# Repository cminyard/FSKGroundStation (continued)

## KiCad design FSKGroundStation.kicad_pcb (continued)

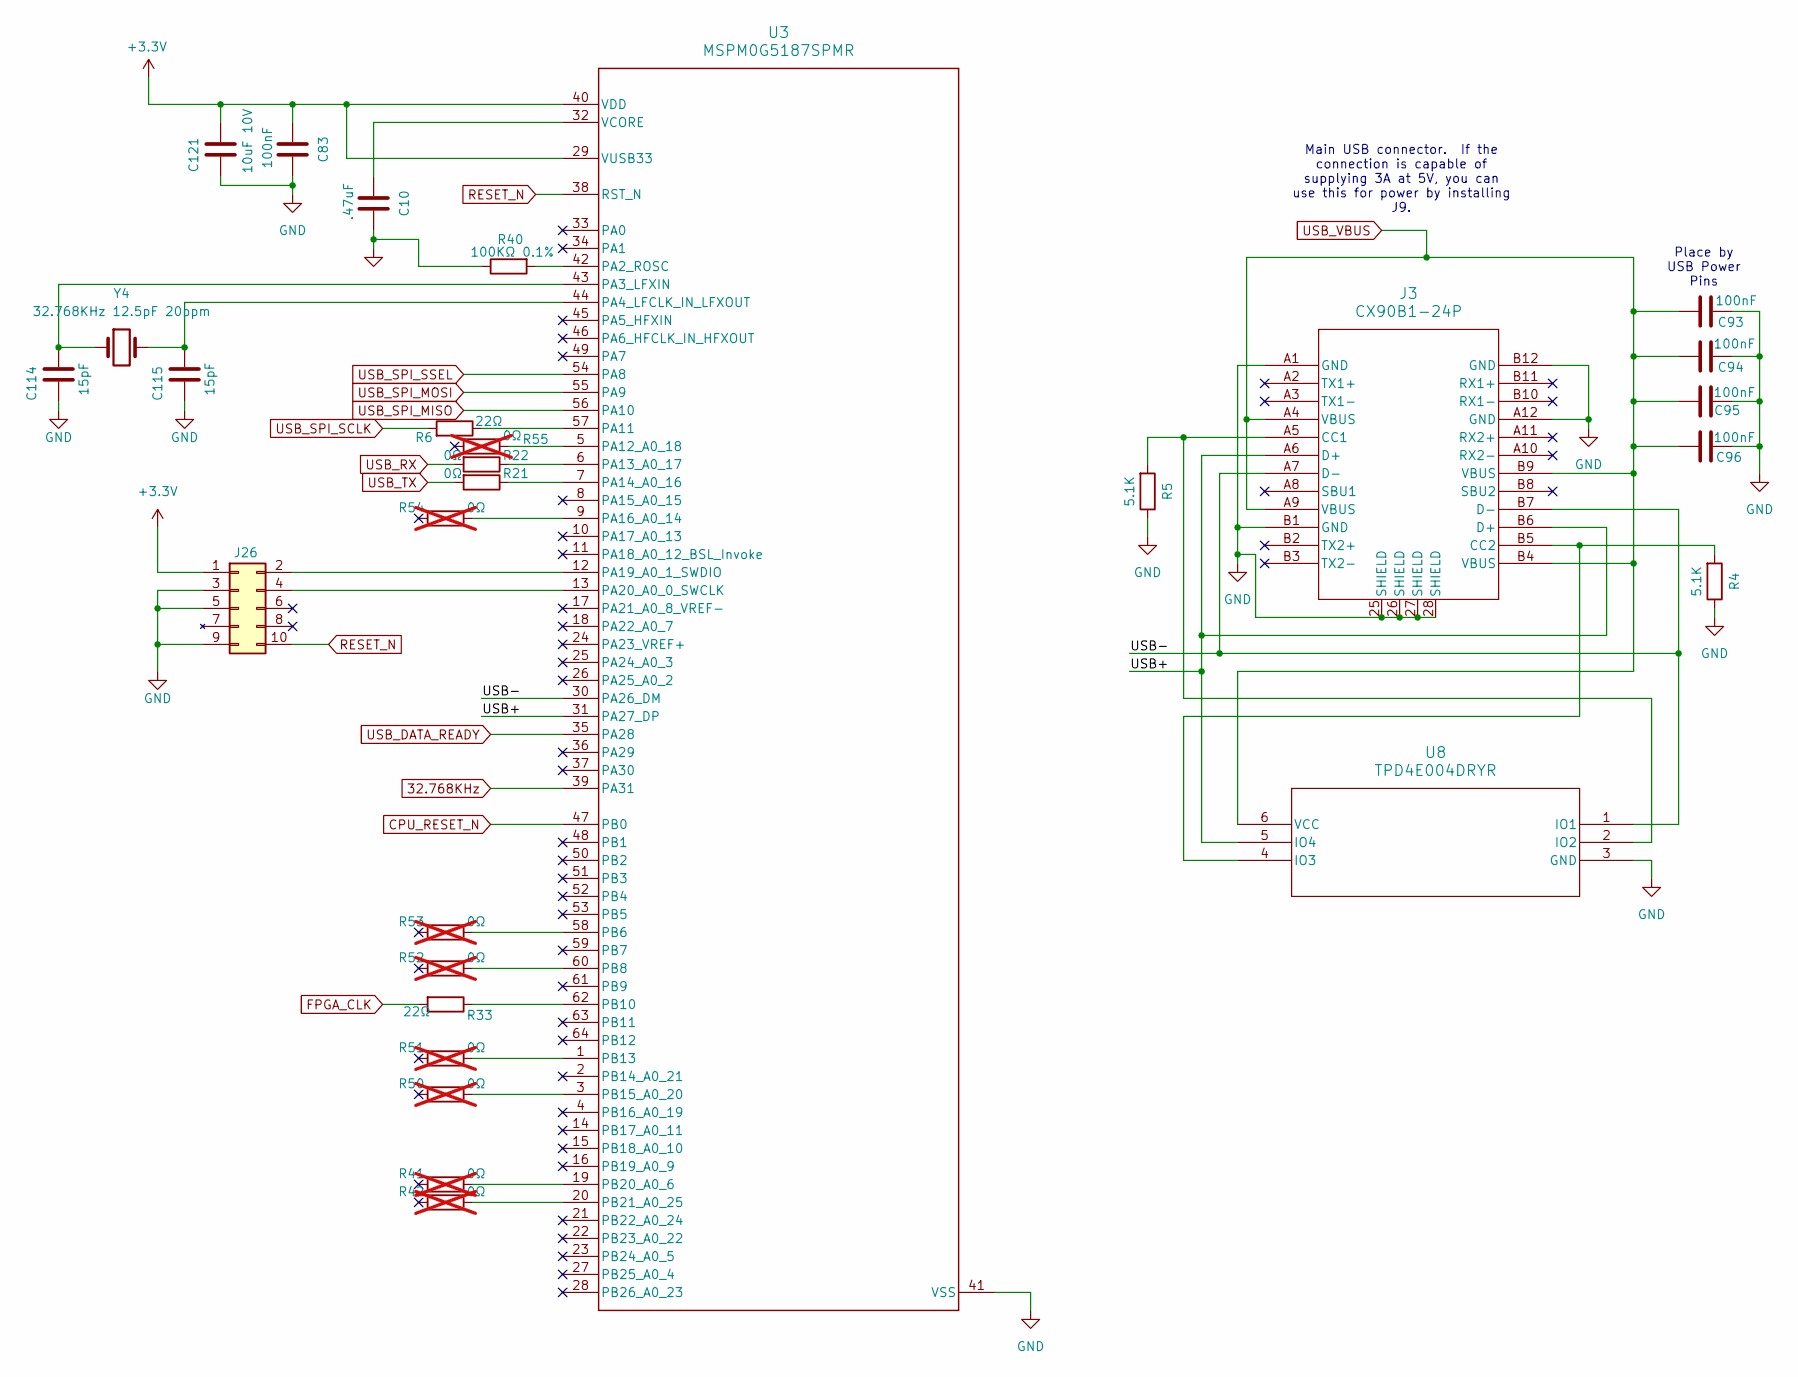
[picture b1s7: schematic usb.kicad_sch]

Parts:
C10: .47uF; C_0603_1608Metric_Pad1.08x0.95mm_HandSolder
C83, C93, C94, C95, C96: 100nF; C_0402_1005Metric
C114, C115: 15pF; C_0402_1005Metric_Pad0.74x0.62mm_HandSolder
C121: 10uF 10V; C_1206_3216Metric_Pad1.33x1.80mm_HandSolder
J3: CX90B1-24P; CX90B1-24P_HIR
J26: FTSH-105-01-L-DV-K
R4, R5: 5.1K; R_0402_1005Metric
R6: 22Ω; R_0402_1005Metric
R21, R22: 0Ω; R_0402_1005Metric
R33: 22Ω; R_0402_1005Metric_Pad0.72x0.64mm_HandSolder
R40: 100KΩ 0.1%; R_0402_1005Metric
R41, R42, R50, R51, R52, R53, R54, R55: 0Ω; R_0402_1005Metric; not fitted
U3: MSPM0G5187SPMR; PM0064A-IPC_A
U8: TPD4E004DRYR; DRY6
Y4: 32.768KHz 12.5pF 20ppm; Crystal_SMD_2012-2Pin_2.0x1.2mm

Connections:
32.768KHz: U3.39 (PA31); also elsewhere on the board
+3.3V: C83.2, C121.2, J26.1 (VTREF), U3.29 (VUSB33), U3.40 (VDD); also elsewhere on the board
/USB/USB+: J3.A6 (D+), J3.B6 (D+), U3.31 (PA27_DP), U8.5 (IO4)
/USB/USB-: J3.A7 (D-), J3.B7 (D-), U3.30 (PA26_DM), U8.1 (IO1)
CPU_RESET_N: U3.47 (PB0); also elsewhere on the board
FPGA_CLK: R33.2; also elsewhere on the board
GND: C10.1, C83.1, C93.2, C94.2, C95.2, C96.2, C114.1, C115.1, C121.1, J3.25 (SHIELD), J3.26 (SHIELD), J3.27 (SHIELD), J3.28 (SHIELD), J3.A1 (GND), J3.A12 (GND), J3.B1 (GND), J3.B12 (GND), J26.3 (GND), J26.5 (GND), J26.9 (GND), R4.1, R5.1, R40.1, U3.41 (VSS), U8.3 (GND); also elsewhere on the board
unnamed: J3.A5 (CC1), R5.2, U8.2 (IO2)
unnamed: J3.B5 (CC2), R4.2, U8.4 (IO3)
unnamed: J26.4 (TCK), U3.13 (PA20_A0_0_SWCLK)
unnamed: J26.2 (TMS), U3.12 (PA19_A0_1_SWDIO)
unnamed: R40.2, U3.42 (PA2_ROSC)
unnamed: C114.2, U3.43 (PA3_LFXIN), Y4.1
unnamed: C115.2, U3.44 (PA4_LFCLK_IN_LFXOUT), Y4.2
unnamed: R6.1, U3.57 (PA11)
unnamed: R55.1, U3.5 (PA12_A0_18)
unnamed: R22.1, U3.6 (PA13_A0_17)
unnamed: R21.1, U3.7 (PA14_A0_16)
unnamed: R54.1, U3.9 (PA16_A0_14)
unnamed: R53.1, U3.58 (PB6)
unnamed: R52.1, U3.60 (PB8)
unnamed: R33.1, U3.62 (PB10)
unnamed: R51.1, U3.1 (PB13)
unnamed: R50.1, U3.3 (PB15_A0_20)
unnamed: R41.1, U3.19 (PB20_A0_6)
unnamed: R42.1, U3.20 (PB21_A0_25)
unnamed: C10.2, U3.32 (VCORE)
RESET_N: J26.10 (NRST), U3.38 (RST_N); also elsewhere on the board
USB_DATA_READY: U3.35 (PA28); also elsewhere on the board
USB_RX: R22.2; also elsewhere on the board
USB_SPI_MISO: U3.56 (PA10); also elsewhere on the board
USB_SPI_MOSI: U3.55 (PA9); also elsewhere on the board
USB_SPI_SCLK: R6.2; also elsewhere on the board
USB_SPI_SSEL: U3.54 (PA8); also elsewhere on the board
USB_TX: R21.2; also elsewhere on the board
USB_VBUS: C93.1, C94.1, C95.1, C96.1, J3.A4 (VBUS), J3.A9 (VBUS), J3.B4 (VBUS), J3.B9 (VBUS), U8.6 (VCC); also elsewhere on the board

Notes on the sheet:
Place by USB Power Pins
Main USB connector. If the connection is capable of supplying 3A at 5V, you can use this for power by installing J9.

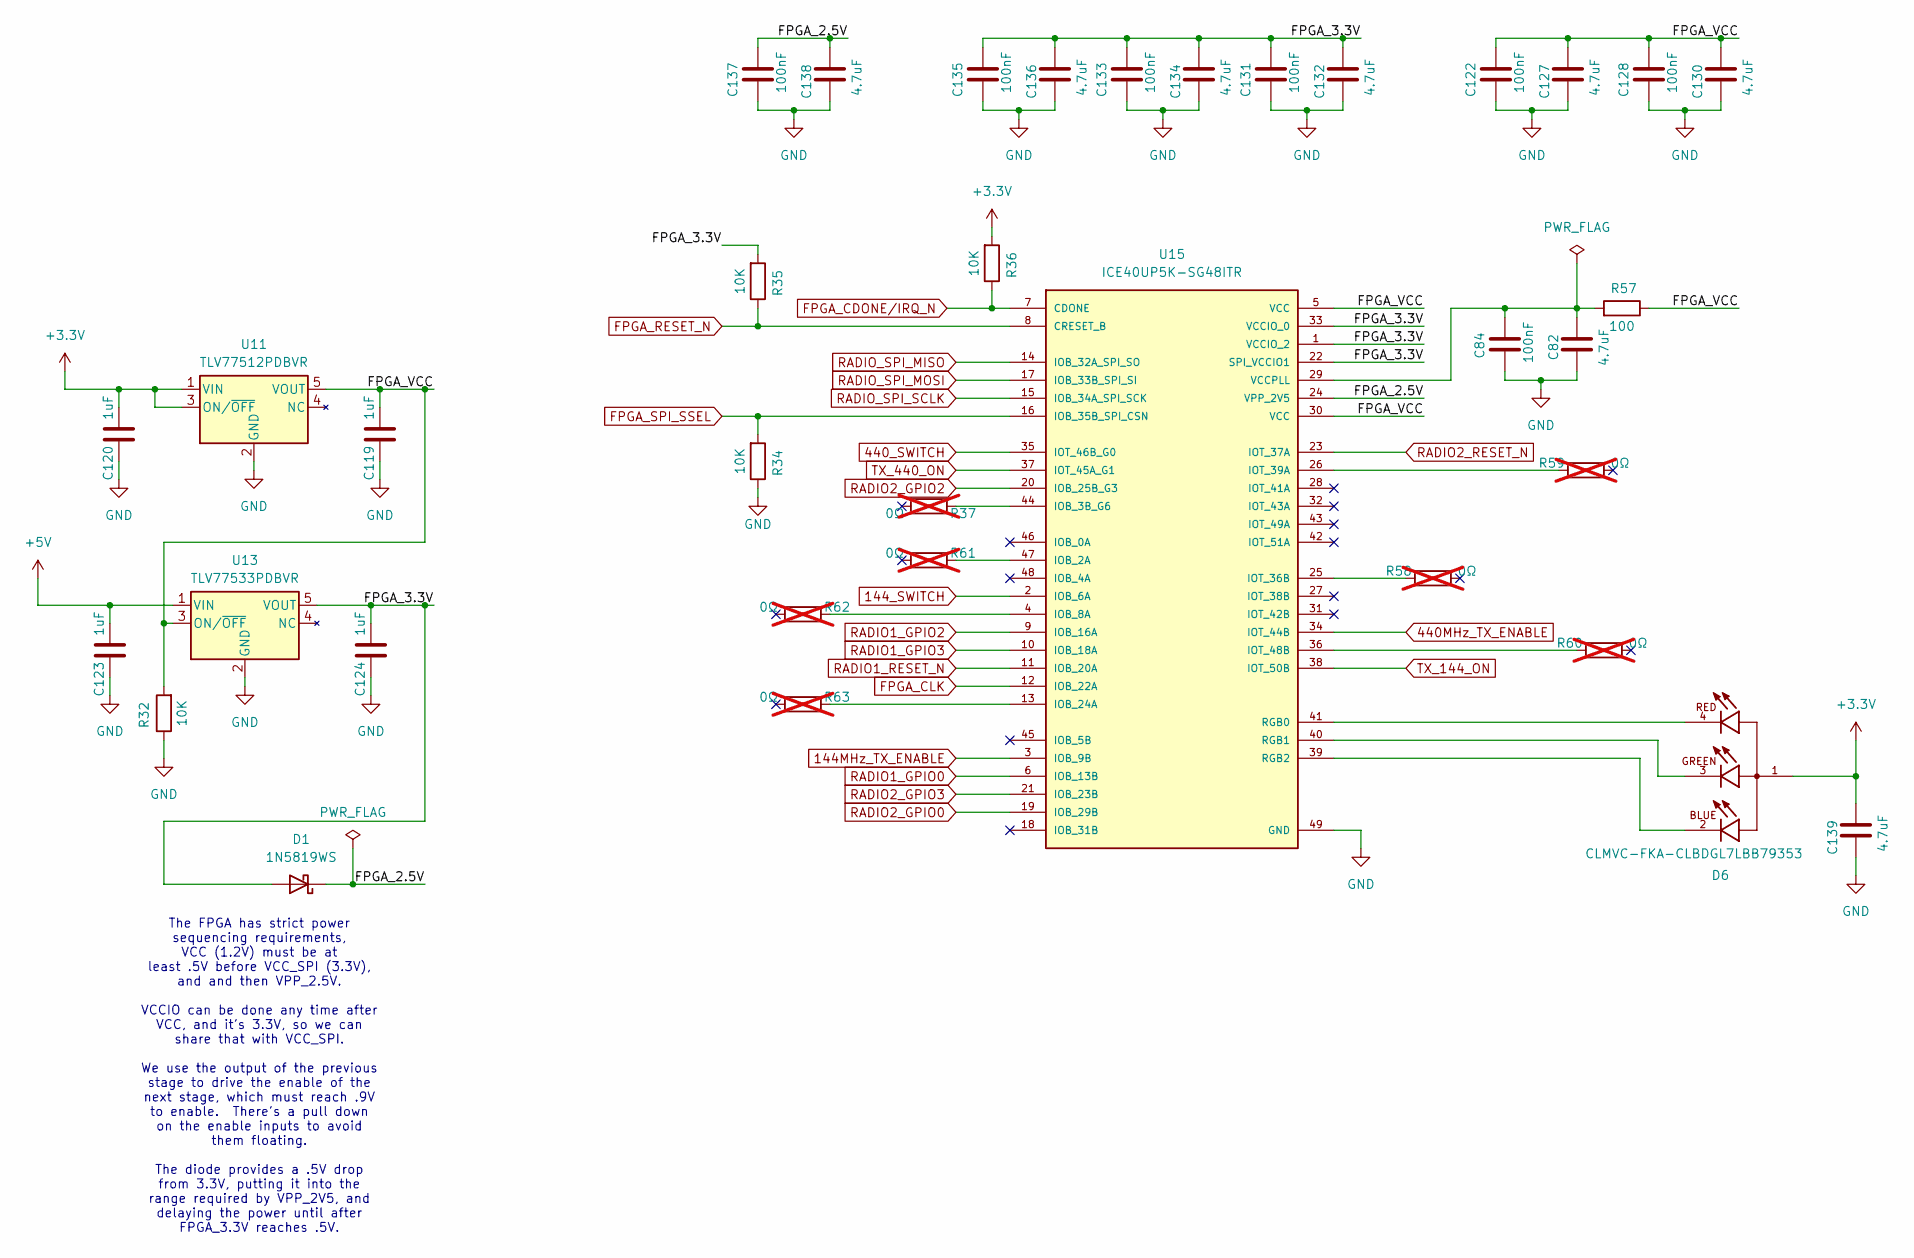
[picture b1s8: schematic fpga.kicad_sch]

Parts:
C82, C127, C130, C132, C134, C136, C138, C139: 4.7uF; C_0603_1608Metric_Pad1.08x0.95mm_HandSolder
C84, C122, C128, C131, C133, C135, C137: 100nF; C_0402_1005Metric_Pad0.74x0.62mm_HandSolder
C119, C120, C123, C124: 1uF; C_0603_1608Metric_Pad1.08x0.95mm_HandSolder
D1: 1N5819WS; D_SOD-323
D6: CLMVC-FKA-CLBDGL7LBB79353; LED_CLMVC-FKA-CLBDGL7LBB79353; PARTREV 14
R32, R34, R35, R36: 10K; R_0402_1005Metric
R37, R58, R59, R60, R61, R62, R63: 0Ω; R_0402_1005Metric_Pad0.72x0.64mm_HandSolder; not fitted
R57: 100; R_0402_1005Metric
U11: TLV77512PDBVR; SOT-23-5
U13: TLV77533PDBVR; SOT-23-5
U15: ICE40UP5K-SG48ITR; QFN50P700X700X100-49N; DigiKey_Part_Number 220-2155-1-ND

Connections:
144MHz_TX_ENABLE: U15.3 (IOB_9B); also elsewhere on the board
144_SWITCH: U15.2 (IOB_6A); also elsewhere on the board
440MHz_TX_ENABLE: U15.34 (IOT_44B); also elsewhere on the board
440_SWITCH: U15.35 (IOT_46B_G0); also elsewhere on the board
+3.3V: C120.2, C139.2, D6.1, R36.2, U11.1 (VIN), U11.3 (ON/~OFF); also elsewhere on the board
+5V: C123.2, U13.1 (VIN); also elsewhere on the board
/FPGA/FPGA_2.5V: C137.2, C138.2, D1.1 (K), U15.24 (VPP_2V5)
/FPGA/FPGA_3.3V: C124.2, C131.2, C132.2, C133.2, C134.2, C135.2, C136.2, D1.2 (A), R35.2, U13.5 (VOUT), U15.1 (VCCIO_2), U15.22 (SPI_VCCIO1), U15.33 (VCCIO_0)
/FPGA/FPGA_VCC: C119.2, C122.2, C127.2, C128.2, C130.2, R32.2, R57.1, U11.5 (VOUT), U13.3 (ON/~OFF), U15.5 (VCC), U15.30 (VCC)
FPGA_CDONE/IRQ_N: R36.1, U15.7 (CDONE); also elsewhere on the board
FPGA_CLK: U15.12 (IOB_22A); also elsewhere on the board
FPGA_RESET_N: R35.1, U15.8 (CRESET_B); also elsewhere on the board
FPGA_SPI_SSEL: R34.2, U15.16 (IOB_35B_SPI_CSN); also elsewhere on the board
GND: C82.1, C84.1, C119.1, C120.1, C122.1, C123.1, C124.1, C127.1, C128.1, C130.1, C131.1, C132.1, C133.1, C134.1, C135.1, C136.1, C137.1, C138.1, C139.1, R32.1, R34.1, U11.2 (GND), U13.2 (GND), U15.49 (GND); also elsewhere on the board
unnamed: R61.1, U15.47 (IOB_2A)
unnamed: R37.1, U15.44 (IOB_3B_G6)
unnamed: R62.1, U15.4 (IOB_8A)
unnamed: R63.1, U15.13 (IOB_24A)
unnamed: R58.1, U15.25 (IOT_36B)
unnamed: R59.1, U15.26 (IOT_39A)
unnamed: R60.1, U15.36 (IOT_48B)
unnamed: D6.4, U15.41 (RGB0)
unnamed: D6.3, U15.40 (RGB1)
unnamed: D6.2, U15.39 (RGB2)
unnamed: C82.2, C84.2, R57.2, U15.29 (VCCPLL)
RADIO1_GPIO0: U15.6 (IOB_13B); also elsewhere on the board
RADIO1_GPIO2: U15.9 (IOB_16A); also elsewhere on the board
RADIO1_GPIO3: U15.10 (IOB_18A); also elsewhere on the board
RADIO1_RESET_N: U15.11 (IOB_20A); also elsewhere on the board
RADIO2_GPIO0: U15.19 (IOB_29B); also elsewhere on the board
RADIO2_GPIO2: U15.20 (IOB_25B_G3); also elsewhere on the board
RADIO2_GPIO3: U15.21 (IOB_23B); also elsewhere on the board
RADIO2_RESET_N: U15.23 (IOT_37A); also elsewhere on the board
RADIO_SPI_MISO: U15.14 (IOB_32A_SPI_SO); also elsewhere on the board
RADIO_SPI_MOSI: U15.17 (IOB_33B_SPI_SI); also elsewhere on the board
RADIO_SPI_SCLK: U15.15 (IOB_34A_SPI_SCK); also elsewhere on the board
TX_144_ON: U15.38 (IOT_50B); also elsewhere on the board
TX_440_ON: U15.37 (IOT_45A_G1); also elsewhere on the board

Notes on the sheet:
The FPGA has strict power sequencing requirements, VCC (1.2V) must be at least .5V before VCC_SPI (3.3V), and and then VPP_2.5V. VCCIO can be done any time after VCC, and it's 3.3V, so we can share that with VCC_SPI. We use the output of the previous stage to drive the enable of the next stage, whi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

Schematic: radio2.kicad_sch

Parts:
C14: 10nF; C_0402_1005Metric_Pad0.74x0.62mm_HandSolder
C16, C29: 1nF; C_0402_1005Metric_Pad0.74x0.62mm_HandSolder
C17, C18, C19, C20, C21, C22, C23, C24, C25, C26, C27: 47nF; C_0402_1005Metric_Pad0.74x0.62mm_HandSolder
C28: 220nF; C_0402_1005Metric_Pad0.74x0.62mm_HandSolder
C49: 39pF 1%; C_0402_1005Metric_Pad0.74x0.62mm_HandSolder
C53: 56pF 1%; C_0402_1005Metric_Pad0.74x0.62mm_HandSolder
C85: 100nF; C_0402_1005Metric_Pad0.74x0.62mm_HandSolder
L18: 56nH; L_0603_1608Metric_Pad1.05x0.95mm_HandSolder
R7: 56K 1%; R_0402_1005Metric
R14: 0Ω; R_0402_1005Metric
R16: 18Ω; R_0402_1005Metric
R31: 0Ω; R_0402_1005Metric; not fitted
U14: CC1125RHBR; RHB32_3P45X3P45_TEX
Y1: OW2EL89CENUXK7YLC-40M; Oscillator_SMD_SiT_PQFN-4Pin_2.0x1.6mm

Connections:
440_PA: C49.2; also elsewhere on the board
440_RX_N: U14.20 (LNA_N); also elsewhere on the board
440_RX_P: U14.19 (LNA_P); also elsewhere on the board
440_TRX_SW: U14.18 (TRX_SW); also elsewhere on the board
+3.3V: C19.2, C20.2, C21.2, C22.2, C23.2, C24.2, C25.2, C26.2, C27.2, C53.2, C85.2, R16.2, U14.1 (VDD_GUARD), U14.5 (DVDD), U14.12 (DVDD), U14.13 (AVDD_IF), U14.15 (AVDD_RF), U14.22 (AVDD_SYNTH1), U14.25 (AVDD_PFD_CHP), U14.27 (AVDD_SYNTH2), U14.28 (AVDD_XOSC), Y1.4 (V+); also elsewhere on the board
GND: C14.1, C17.1, C18.1, C19.1, C20.1, C21.1, C22.1, C23.1, C24.1, C25.1, C26.1, C27.1, C28.1, C85.1, R7.1, R31.1, U14.30 (XOSC_Q1), U14.33 (EPAD), Y1.2 (GND); also elsewhere on the board
unnamed: C29.2, R14.1, R31.2
unnamed: C53.1, L18.2, R16.1
unnamed: C28.2, U14.6 (DCPL)
unnamed: C18.2, U14.26 (DCPL_PFD_CHP)
unnamed: C14.2, U14.21 (DCPL_VCO)
unnamed: C17.2, U14.29 (DCPL_XOSC)
unnamed: C29.1, U14.32 (EXT_XOSC)
unnamed: C16.1, U14.23 (LPF0)
unnamed: C16.2, U14.24 (LPF1)
unnamed: C49.1, L18.1, U14.17 (PA)
unnamed: R7.2, U14.14 (RBIAS)
unnamed: R14.2, Y1.3 (OUT)
RADIO2_GPIO0: U14.10 (GPIO0); also elsewhere on the board
RADIO2_GPIO2: U14.4 (GPIO2); also elsewhere on the board
RADIO2_GPIO3: U14.3 (GPIO3); also elsewhere on the board
RADIO2_RESET_N: U14.2 (RESET_N); also elsewhere on the board
RADIO2_SPI_SSEL: U14.11 (CSN); also elsewhere on the board
RADIO_SPI_MISO: U14.9 (SO(GPIO1)); also elsewhere on the board
RADIO_SPI_MOSI: U14.7 (SI); also elsewhere on the board
RADIO_SPI_SCLK: U14.8 (SCLK); also elsewhere on the board

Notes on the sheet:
This is in case we need to reduce the voltage into the oscillator pin.
Decoupling, place one by each power pin.

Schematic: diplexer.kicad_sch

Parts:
C112: 5pF ±.1; C_0402_1005Metric_Pad0.74x0.62mm_HandSolder
C129: 14pF 1%; C_0402_1005Metric_Pad0.74x0.62mm_HandSolder
J22: BWSMA-KWE-Z001; CONN_BWSMA-KWE-Z001_BAT
J23: SJ-3524-SMT; CUI_SJ-3524-SMT; PARTREV 1.03
L23, L24, L40: 470nH; L_0805_2012Metric_Pad1.05x1.20mm_HandSolder
L35: 220nH 2%; L_0805_2012Metric_Pad1.05x1.20mm_HandSolder
L44: 27nH 2%; L_0603_1608Metric_Pad1.05x0.95mm_HandSolder
Q1, Q2: BSS138; SOT-23
R25, R26: 10K; R_0402_1005Metric
R27, R28, R97: 10K; R_0402_1005Metric_Pad0.72x0.64mm_HandSolder

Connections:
GND: J22.2, J22.3, J22.4, J22.5, J23.1, Q1.2 (S), Q2.2 (S), R25.1, R26.1, R27.2, R28.2, R97.2; also elsewhere on the board
unnamed: C112.2, L35.1
unnamed: C129.1, L44.2
unnamed: J22.1, L24.1, L35.2, L44.1
unnamed: L23.2, R27.1
unnamed: L24.2, R28.1
unnamed: L40.2, R97.1
unnamed: J23.2, Q1.3 (D)
unnamed: J23.3, Q2.3 (D)
RF_144: C112.1, L23.1; also elsewhere on the board
RF_440: C129.2, L40.1; also elsewhere on the board
TX_144_ON: Q2.1 (G), R26.2; also elsewhere on the board
TX_440_ON: Q1.1 (G), R25.2; also elsewhere on the board

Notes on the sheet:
Inductor to bleed off static build up on the antenna.
Combined 144/440 antenna port. You lose 1dB using this.
Control output for controlling external things like amplifiers. Open when receiving, short to ground when transmitting.

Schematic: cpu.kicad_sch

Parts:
C2, C3, C4, C5, C6, C7, C8, C9, C108, C109, C110: 100nF; C_0402_1005Metric_Pad0.74x0.62mm_HandSolder
C15: 10uF; C_1206_3216Metric_Pad1.33x1.80mm_HandSolder
C111, C113: 0; C_0402_1005Metric_Pad0.74x0.62mm_HandSolder; not fitted
D4: YELLOW LED; LED_0603_1608Metric_Pad1.05x0.95mm_HandSolder
J1: FTSH-105-01-L-DV-K
J24: HTSW-103-07-G-S; CON3_1X3_TU_TSW
L2: 6.8uH; L_1210_3225Metric_Pad1.42x2.65mm_HandSolder
R1, R56: 10K; R_0402_1005Metric
R20: 22Ω; R_0402_1005Metric
R39: 3KΩ; R_0603_1608Metric_Pad0.98x0.95mm_HandSolder
R46: 22Ω; R_0402_1005Metric_Pad0.72x0.64mm_HandSolder; not fitted
R47: 0Ω; R_0402_1005Metric_Pad0.72x0.64mm_HandSolder; not fitted
U4: CC2755P105E0WRHAR; RHA40_4P5X4P5
U12: SN74AHC1G09QDCKRQ1; DCK5
Y2: 48MHZ 7PF 20ppm; Crystal_SMD_2016-4Pin_2.0x1.6mm

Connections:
2.4G_ANT: U4.39 (ANT); also elsewhere on the board
32.768KHz: U4.26 (DIO23_X32P); also elsewhere on the board
144_PA_TEMP: U4.21 (DIO19_A6); also elsewhere on the board
440_PA_TEMP: U4.22 (DIO20_A5); also elsewhere on the board
+3.3V: C2.2, C3.2, C4.2, C7.2, C8.2, C9.2, D4.2 (A), J1.1 (VTREF), R1.2, R56.2, U4.9 (VDDIO), U4.17 (VDDIO), U4.18 (VDDS), U4.29 (VDDS), U4.31 (VDDS), U4.38 (VDDS), U12.5 (VCC); also elsewhere on the board
/CPU/CPU_RESET2_N: C5.2, J1.10 (NRST), R1.1, U4.25 (nRST), U12.4 (Y)
/CPU/VDDR: C15.2, C108.2, C109.2, C110.2, L2.1, U4.1 (VDDR), U4.2 (VDDR), U4.34 (VDDR)
CPU_RESET_N: R56.1, U12.1 (A); also elsewhere on the board
FPGA_CDONE/IRQ_N: U4.20 (DIO18_A7); also elsewhere on the board
FPGA_RESET_N: U4.16 (DIO16); also elsewhere on the board
FPGA_SPI_SSEL: U4.23 (DIO21_A4); also elsewhere on the board
GND: C2.1, C3.1, C4.1, C5.1, C6.1, C7.1, C8.1, C9.1, C15.1, C108.1, C109.1, C110.1, C111.1, C113.1, J1.3 (GND), J1.5 (GND), J1.9 (GND), J24.3, U4.40 (RFGND), U4.41 (EPAD), U12.3 (GND), Y2.2 (G), Y2.4 (G); also elsewhere on the board
unnamed: D4.1 (K), R39.1
unnamed: L2.2, U4.30 (DCDC_SW)
unnamed: R39.2, U4.3 (DIO0)
unnamed: R20.2, U4.15 (DIO15)
unnamed: R46.1, U4.27 (DIO24_X32N)
unnamed: R47.1, U4.33 (DIO28_A0)
unnamed: C6.2, U4.28 (VDDD)
unnamed: C111.2, U4.36 (X48N), Y2.1
unnamed: C113.2, U4.35 (X48P), Y2.3
RADIO1_SPI_SSEL: U4.24 (DIO22_A3); also elsewhere on the board
RADIO2_SPI_SSEL: U4.19 (DIO17_A8); also elsewhere on the board
RADIO_SPI_MISO: U4.14 (DIO12); also elsewhere on the board
RADIO_SPI_MOSI: U4.13 (DIO11); also elsewhere on the board
RADIO_SPI_SCLK: R20.1; also elsewhere on the board
RESET_N: U12.2 (B); also elsewhere on the board
SWDCK: J1.4 (TCK), U4.11 (DIO9_SWDIO)
SWDIO: J1.2 (TMS), U4.12 (DIO10_SWDCK)
USB_DATA_READY: U4.32 (DIO27_A1); also elsewhere on the board
USB_RX: J24.1, U4.4 (DIO1); also elsewhere on the board
USB_SPI_MISO: U4.8 (DIO5); also elsewhere on the board
USB_SPI_MOSI: U4.7 (DIO4); also elsewhere on the board
USB_SPI_SCLK: U4.6 (DIO3); also elsewhere on the board
USB_SPI_SSEL: U4.10 (DIO7); also elsewhere on the board
USB_TX: J24.2, U4.5 (DIO2); also elsewhere on the board

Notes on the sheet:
TODO - VDDR can also be supplied using an internal LDO, look into that so we can get rid of these parts.
The USB interface provides a 32.768KHz clock, we use that here.

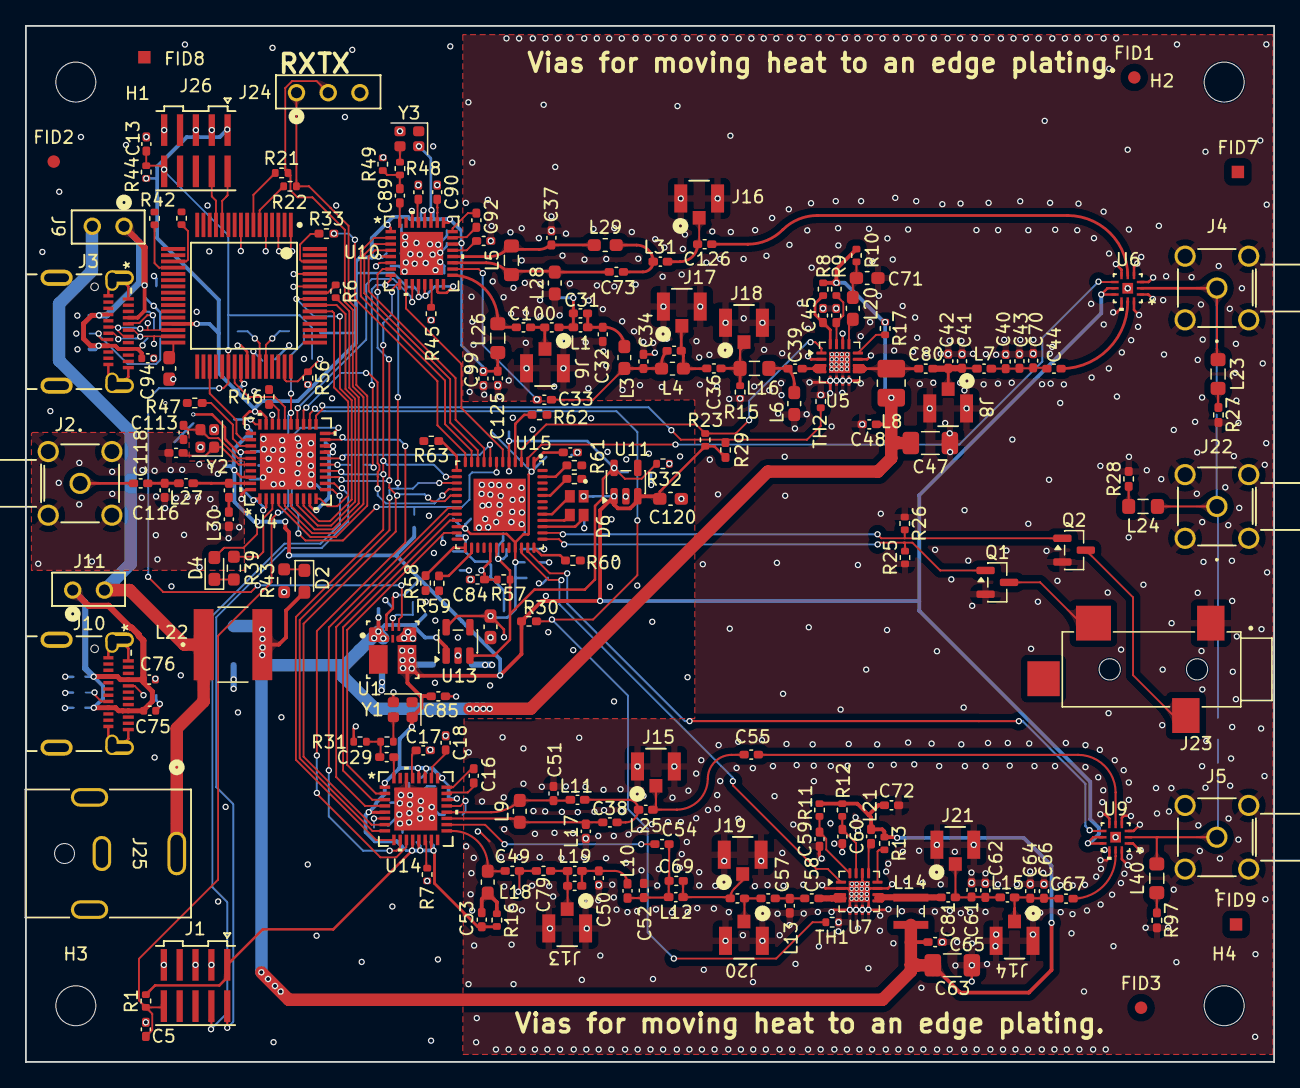
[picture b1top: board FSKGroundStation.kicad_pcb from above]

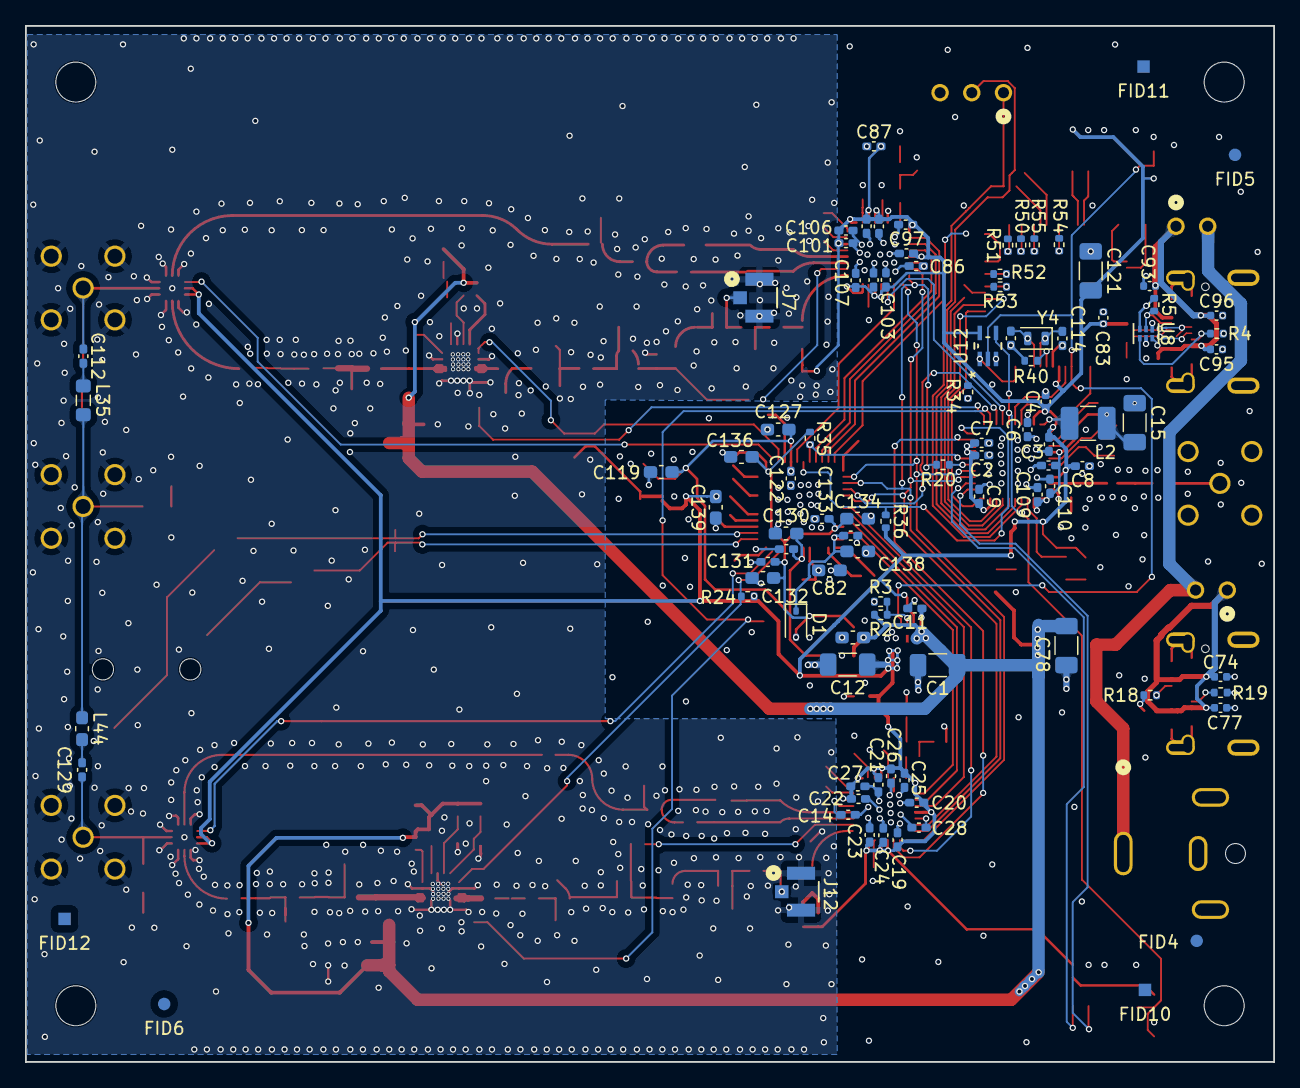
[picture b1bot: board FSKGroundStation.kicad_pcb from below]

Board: 4 copper layers, 100.0 x 83.0 mm, 304 parts (96 on the bottom side), 176 nets.

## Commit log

2026-03-01 Finish up inputting things
2026-03-01 Clean up schematics
2026-03-01 More cleanups and add some test points
2026-03-01 Add more test points
2026-03-01 Start on PCB
    Clean up a lot of issues.
2026-03-01 Layout work
2026-03-02 Finish layout
2026-03-02 Add some things missed in the previous commit
2026-03-02 More little tweaks
2026-03-02 More layout tweaks
2026-03-02 More track cleanup
    Add teardrops, etc.
2026-03-02 Reduce hole sizes and add more holes on PA
    Meet spec requirements.
2026-03-02 Increase power trace widths
    1mm for main +5V.
2026-03-02 Start working on BOM, fix supply indoctors
2026-03-02 More BOM work
2026-03-02 Fix the value of a capacitor
    It was 27pF, not 28pF.
2026-03-02 Add fiducials to the board
2026-03-03 Add fiduciaries and a control output
2026-03-03 Add pull up on the PA enables
    So they are off by default.
2026-03-03 Track cleanups
2026-03-03 Add pulldowns on the external control transistor inputs
    So they are disabled by default.
2026-03-03 Change a resistor on the 150MHz TX
    No need to have a 2K and a 1.96K resistor for this, just use 1.96K
    on both.
2026-03-03 Add bleed-off inductor/resistors to the antenna jacks
2026-03-03 Add a barrel-type power connector
    Make supplying power a little simpler.
2026-03-03 Fix the 440 PA to work at 430-450
2026-03-03 Move RF parts from the bottom of the board to the top
    This will allow a heat sink to be more easily mounted.
2026-03-03 Add thermsistors by the PAs
2026-03-03 Adjust the thermsistors a bit
    Keep the bottom ground plan as clean as possible, make sure there are
    plenty of vias around the termsistor, and avoid messing up the coplanar
    areas around some RF traces.
2026-03-03 Forgot to do a save on the previous commit
2026-03-03 Increase the board width to 82.5mm
    To be sure it will work in the chassis.
2026-03-03 Increase the board width to 83mm
    The slot it's supposed to go into is 84mm wide, it appears 82mm in the
    middle. 83mm should be good.
    According to a post on Amazon, the length is 103mm total with the inside
    dimension 100mm.
2026-03-04 Add some more notes on heat sink options
2026-03-04 Rework the cc1125 matching networks
    Per combining information from the 169MHz PA design (to separate the PA
    and LNA outputs) and the 440 design (to get the component values).
2026-03-04 Control the 440 switch directly from the CPU
    The RX/TX switch on the CC1125 added a lot of complexity with the inverter
    and such. Instead, just drive it frmo the CC1125.
    Use the RX/TX switch on the CC1125 as an option shown on the design with
    169MHz and an external PA, not populated.
2026-03-04 Add some miscellaneous vias
2026-03-04 More vias
    Make sure the grounds are well connected.
2026-03-04 Add an item to the BOM from the recent changes
2026-03-04 Adjust the location of a U.FL test connector
    Put it at the input of the 440 LNA match, it moved since an inductor was
    added.
2026-03-04 Yet more vias
2026-03-04 Directly power the oscillators
    There is only one D/A converter on the CC1312R, so you really couldn't
    power both of the oscillators from that chip. Power is not a concern,
    so just directly power them from 3.3V. That required using a different
    oscillator chip, too, but it was available on both frequencies.
2026-03-04 Fix the BOM for the previous change
2026-03-04 Fix some oscillator issues
    Ground an unused oscillator line on the CC1125 that needs to be grounded
    in external oscillator mode.
    Add a resistor divider to the oscillator inputs in case the voltage
    needs to be decreased. It should be fixable with the internal capacitor
    tuning, but just in case.
2026-03-04 Make a bunch of GPIOs more easily available
    Put them on DNP zero-ohm resistors.
2026-03-04 Forgot to do a save before the last commit.
2026-03-04 Add a bunch of vias for moving heat to an edge plate
    The theory is you can do edge plating on the board and have the heat
    move from the PA, through the various ground layers on the board to
    the vias, then through the edge plate to the chassis.
2026-03-05 Minor track cleanups
2026-03-06 Start a NOTES file as a design log
2026-03-07 First start at reworking to get HDLC
2026-03-09 More re-layout for the new design
2026-03-09 Finish initial layet
2026-03-09 Clean up all violations
2026-03-09 Fix CC2745 layout
    Some pins were wrong.
    Also clean up a lot of layout issues caused by setting the clearance so
    low to get the FPGA to route. Set it back to normal constraints and
    mark all the FPGA exclusions.
2026-03-09 Change the cc2745 to a cc2755
    Same pinout, cheaper, not automotive.
2026-03-09 Add some vias
2026-03-09 One more part
2026-03-10 Fix a wrong component value on 2.5GHz
2026-03-10 Fix some layout issues with recent changes
2026-03-10 More from the previous change
2026-03-10 More teardrops
    For new parts
2026-03-10 Add some LEDs
2026-03-10 Fix some components messed up by the previous change
2026-03-11 Rewire the radio SPI pins
    They couldn't go on the pins they were on.
2026-03-11 More track cleanups for USB and the CPU
    Make things a little neater.
2026-03-11 Fix a design rule warning.
2026-03-11 Use a diode to provide the 2.5V voltage for the FPGA
    Drops 3.3V down to 2.8V, which is in range. It's a lot simpler.
    Also do some via cleanup.
2026-03-11 Add a DNP resistor on an FPGA pin
    Make it available for use. Clean up routing around the FPGA a bit, too.
2026-03-11 Switch to a CPU with a USB interface for the USB connection
    The part that was picked had proprietary tools and configuration and it
    didn't support interrupts. The CPU is cheaper and more capable.
2026-03-11 Add a blue LED to the power line
2026-03-11 Add some missing footprints
2026-03-11 Missed the schematic save on the new LED
2026-03-12 Track cleanup around the USB
    Make things cleaner.
2026-03-12 Add a clock from the USB chip to the FPGA
    The FPGA might need a clock for certain things, so provide it.
2026-03-13 Split the USB CPU and main CPU reset lines
2026-03-13 Split the CPU reset line a little better
    Make it so either the main reset line or the reset line from the USB
    device will reset the CPU.
2026-03-13 Move he FPGA clock to pin 62 on the USB chip
    That is easily drivable with PWM, if I can figure out how that works.
2026-03-14 Fix some BOM issues
2026-03-16 Add DNP resistors on the unused pins of the CPU and the USB chip
    Move a few things to improve the layout, too.
2026-03-16 Move the diplexer parts close to the sources
    So there's not a big stub when not using the diplexer.
2026-03-17 Some notes and via and track fixes
2026-03-20 Move the GPIOs for heat removal closer to the edge
    The need to be in contact with the chassis.
2026-03-20 Move a note
2026-04-05 More work
2026-04-07 Replace the FPGA with a QFP one
    It has more pins, which might be useful, and it's easier to work with
    than the BGA. It also has a built-in SPI. It's currently an ICE40UP5K,
    but the ICE5LP[124]K chips are pin compatible and cheaper.
2026-05-08 Add more cleanups and docs
